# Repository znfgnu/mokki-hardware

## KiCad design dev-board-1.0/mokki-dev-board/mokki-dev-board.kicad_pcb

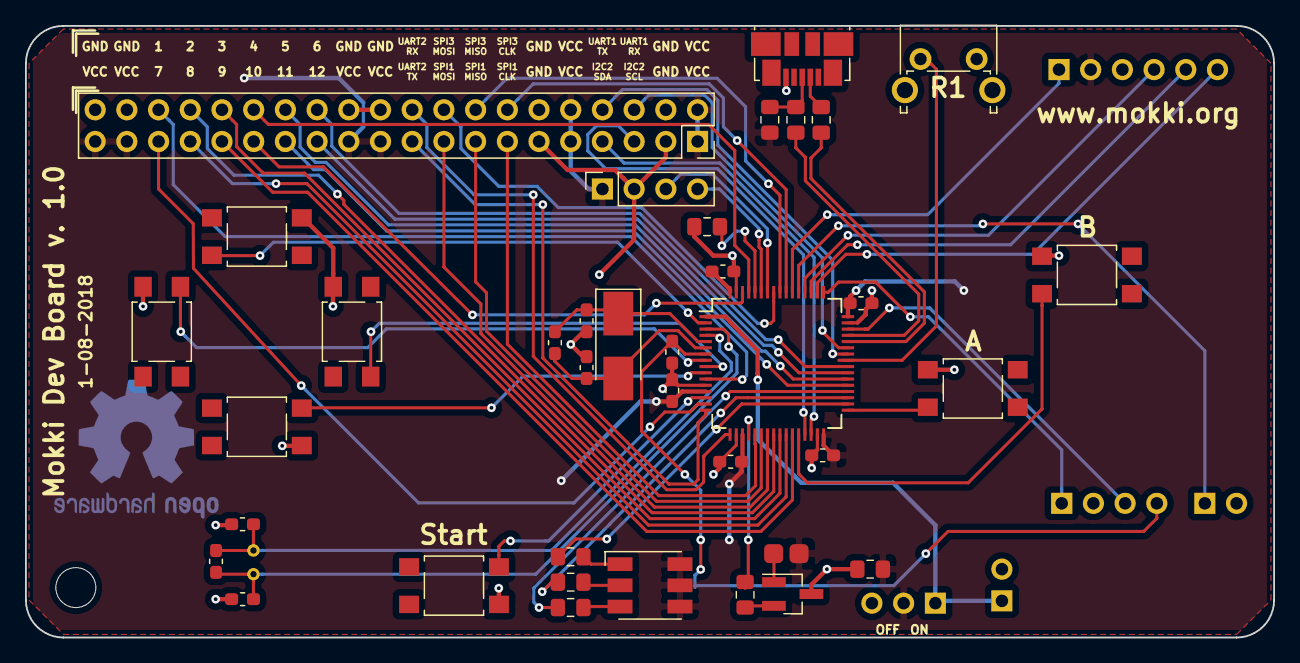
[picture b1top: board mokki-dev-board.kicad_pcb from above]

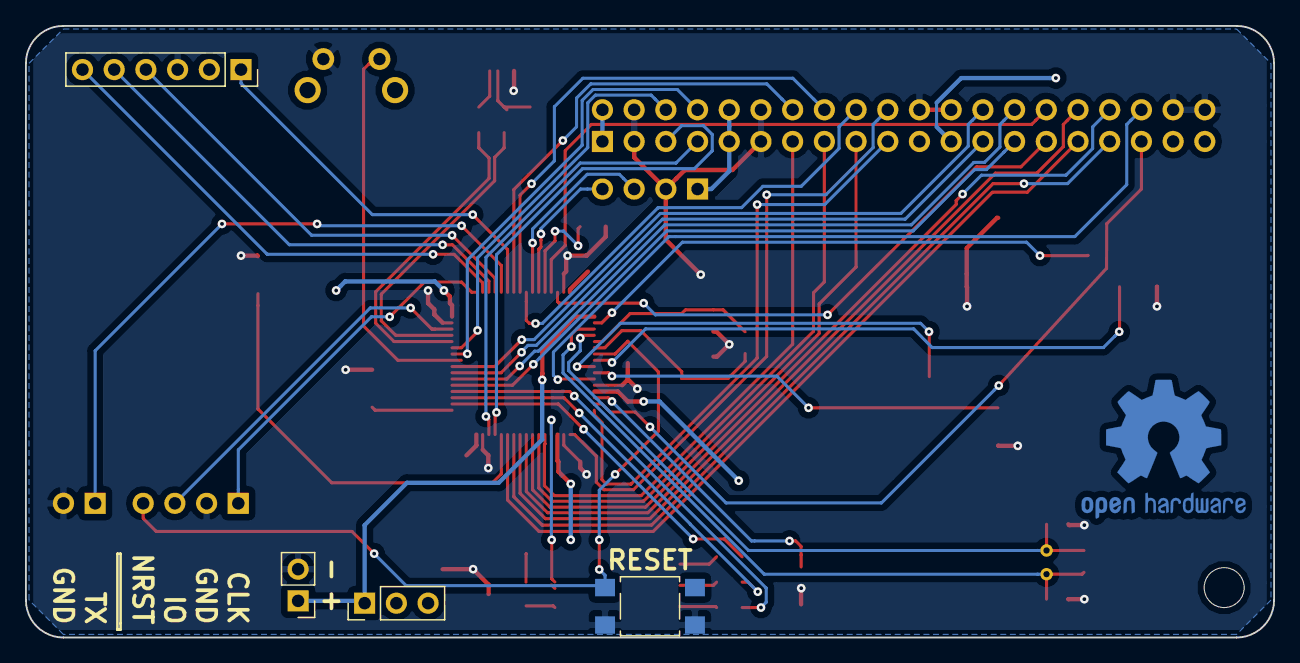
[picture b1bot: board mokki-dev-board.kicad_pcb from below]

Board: 2 copper layers, 100.0 x 49.0 mm, 44 parts (4 on the bottom side), 63 nets.

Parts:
BT1: Battery; PinHeader_1x02_P2.54mm_Vertical
C1, C3: 22p; C_0603_1608Metric_Pad1.05x0.95mm_HandSolder
C2, C4: 100p; C_0603_1608Metric_Pad1.05x0.95mm_HandSolder
C5, C6, C7, C8, C10, C11: 100n; C_0603_1608Metric_Pad1.05x0.95mm_HandSolder
C9: 10u; C_0805_2012Metric_Pad1.15x1.40mm_HandSolder
D1: LED_RGB; LED_RGB_5050-6
J1: USB_B_Micro; USB_Micro-B_Molex_47346-0001
J2: SWD connector; PinSocket_1x04_P2.54mm_Horizontal-no-drawing
J3: OLED_Connector; PinSocket_1x04_P2.54mm_Vertical
J4: BLE_Connector; PinSocket_1x06_P2.54mm_Vertical
J5: DEBUG_Conn; PinSocket_1x02_P2.54mm_Horizontal-no-drawing
J6: User port; PinSocket_2x20_P2.54mm_Vertical
LS1: Speaker; tp-smd-2pad
Q1: BC847B; SOT-23_Handsoldering
R1, R2: R_Small; R_0603_1608Metric_Pad1.05x0.95mm_HandSolder
R3: 1k; R_0805_2012Metric_Pad1.15x1.40mm_HandSolder
R4, R5, R6: 50R; R_0805_2012Metric_Pad1.15x1.40mm_HandSolder
R7: 10K; R_0805_2012Metric_Pad1.15x1.40mm_HandSolder
R8, R9: 22R; R_0805_2012Metric_Pad1.15x1.40mm_HandSolder
R10: 100K; R_0805_2012Metric_Pad1.15x1.40mm_HandSolder
SW1: SW_PWR; PinHeader_1x03_P2.54mm_Vertical
SW2: BTN_RST; SW_SPST_TL3305B
SW3: BTN_UP; SW_SPST_TL3305B
SW4: BTN_HOME; SW_SPST_TL3305B
SW5: BTN_LEFT; SW_SPST_TL3305B
SW6: BTN_R1; SW_Tactile_SPST_Angled_PTS645Vx58-2LFS
SW7: BTN_RIGHT; SW_SPST_TL3305B
SW8: BTN_A; SW_SPST_TL3305B
SW9: BTN_DOWN; SW_SPST_TL3305B
SW10: BTN_B; SW_SPST_TL3305B
U1: STM32F103RCTx; LQFP-64_10x10mm_P0.5mm
Y1: 12M0; Crystal_SMD_5032-2Pin_5.0x3.2mm_HandSoldering
Y2: 32k768; Crystal_C38-LF_D3.0mm_L8.0mm_Horizontal-no-drawing

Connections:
+BATT: BT1.1, SW1.1, U1.1
/DAC: R3.2, U1.20
/GPIO_PA0: SW4.1, U1.14
/GPIO_PA1_AT: J6.35, U1.15
/GPIO_PA8: SW6.1, U1.41
/GPIO_PA15: J4.6, U1.50
/GPIO_PB0_AT: J6.33, U1.26
/GPIO_PB1_AT: J6.31, U1.27
/GPIO_PB2: SW10.1, U1.28
/GPIO_PB8_T: J6.30, U1.61
/GPIO_PB9_T: J6.29, U1.62
/GPIO_PB12: SW8.1, U1.33
/GPIO_PB13: R4.2, U1.34
/GPIO_PB14: R5.2, U1.35
/GPIO_PB15: R6.2, U1.36
/GPIO_PC0: SW5.1, U1.8
/GPIO_PC1: SW7.1, U1.9
/GPIO_PC2: SW9.1, U1.10
/GPIO_PC3_A: J6.36, U1.11
/GPIO_PC4_A: J6.34, U1.24
/GPIO_PC5_A: J6.32, U1.25
/GPIO_PC6_T: J6.27, U1.37
/GPIO_PC7_T: J6.28, U1.38
/GPIO_PC8_T: J6.25, U1.39
/GPIO_PC9_T: J6.26, U1.40
/GPIO_PC13: SW3.1, U1.2
/GPIO_PD2: J4.1, U1.54
/I2C1_SCL: J3.3, U1.58
/I2C1_SDA: J3.4, U1.59
/I2C2_SCL: J6.5, U1.29
/I2C2_SDA: J6.7, U1.30
/NRST: C11.1, J2.4, SW2.1, U1.7
/SPI1_MISO: J6.15, U1.22
/SPI1_MOSI: J6.17, U1.23
/SPI1_SCK: J6.13, U1.21
/SPI3_MISO: J6.16, U1.56
/SPI3_MOSI: J6.18, U1.57
/SPI3_SCK: J6.14, U1.55
/SWD_CLK: J2.1, U1.49
/SWD_IO: J2.3, U1.46
/UART4_RX: J4.4, U1.52
/UART4_TX: J4.5, U1.51
/USART1_RX: J6.6, U1.43
/USART1_TX: J6.8, U1.42
/USART2_RX: J6.20, U1.17
/USART2_TX: J6.19, U1.16
/USART5_TX: J5.1, U1.53
/USB_DM: R8.1, U1.44
/USB_DP: R9.1, U1.45
GND: BT1.2, C1.2, C2.2, C3.2, C4.2, C5.2, C6.2, C7.2, C8.2, C9.2, C10.2, C11.2, J1.5, J2.2, J3.2, J4.3, J5.2, J6.3, J6.4, J6.11, J6.12, J6.22, J6.24, J6.38, J6.40, Q1.3, R10.2, SW2.2, SW3.2, SW4.2, SW5.2, SW6.2, SW7.2, SW8.2, SW9.2, SW10.2, U1.12, U1.18, U1.31, U1.47, U1.63
unnamed: C1.1, R1.2, U1.5, Y1.1
unnamed: C2.1, R2.2, U1.3, Y2.1
unnamed: C3.1, R1.1, U1.6, Y1.2
unnamed: C4.1, R2.1, U1.4, Y2.2
unnamed: D1.1, R4.1
unnamed: D1.2, R5.1
unnamed: D1.3, R6.1
unnamed: J1.2, R8.2
unnamed: J1.3, R7.2, R9.2
unnamed: LS1.2, Q1.1
unnamed: Q1.2, R3.1
unnamed: R10.1, U1.60
VCC: C5.1, C6.1, C7.1, C8.1, C9.1, C10.1, D1.4, D1.5, D1.6, J3.1, J4.2, J6.1, J6.2, J6.9, J6.10, J6.21, J6.23, J6.37, J6.39, LS1.1, R7.1, SW1.2, U1.13, U1.19, U1.32, U1.48, U1.64

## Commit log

2018-07-27 Schematic ready
2018-07-27 Fixed LED - common anode, removed multiple labels, added values to some components
2018-07-28 missing wire
2018-07-30 Footprints assigned
2018-07-30 Fixed user port issue
2018-07-30 Elements initially placed on PCB
2018-07-30 Made some space for connections
2018-07-30 Modified some footprints, used 0603 capacitors
2018-07-30 Final placement (?)
2018-07-30 Silkscreen, buttons placement
2018-07-30 PCB design finished
2018-07-30 board ready to production
2018-07-30 Final touches
2018-07-30 Final version
2018-07-30 FInal version - production files
2018-07-31 Shrinked from 50mm to 45mm
2018-07-31 Revert "FInal version - production files"
    This reverts commit a0387784cc1ff4248ba3dd3fa7136a29c3c8ec96.
2018-07-31 Revert "Revert "FInal version - production files""
    This reverts commit f41fb67aed8f1cfb77300dac5fd141a79cb80eb8.
2018-07-31 Revert "Shrinked from 50mm to 45mm"
    This reverts commit b318c16d80a30d8fc187a8b3fd500b0e07cadd18.
2018-08-01 ready to panelize
2018-08-01 production files (board)
2018-08-01 FIles renamed for GerberPanelizer
2020-07-17 PDF generated, metedata updated
